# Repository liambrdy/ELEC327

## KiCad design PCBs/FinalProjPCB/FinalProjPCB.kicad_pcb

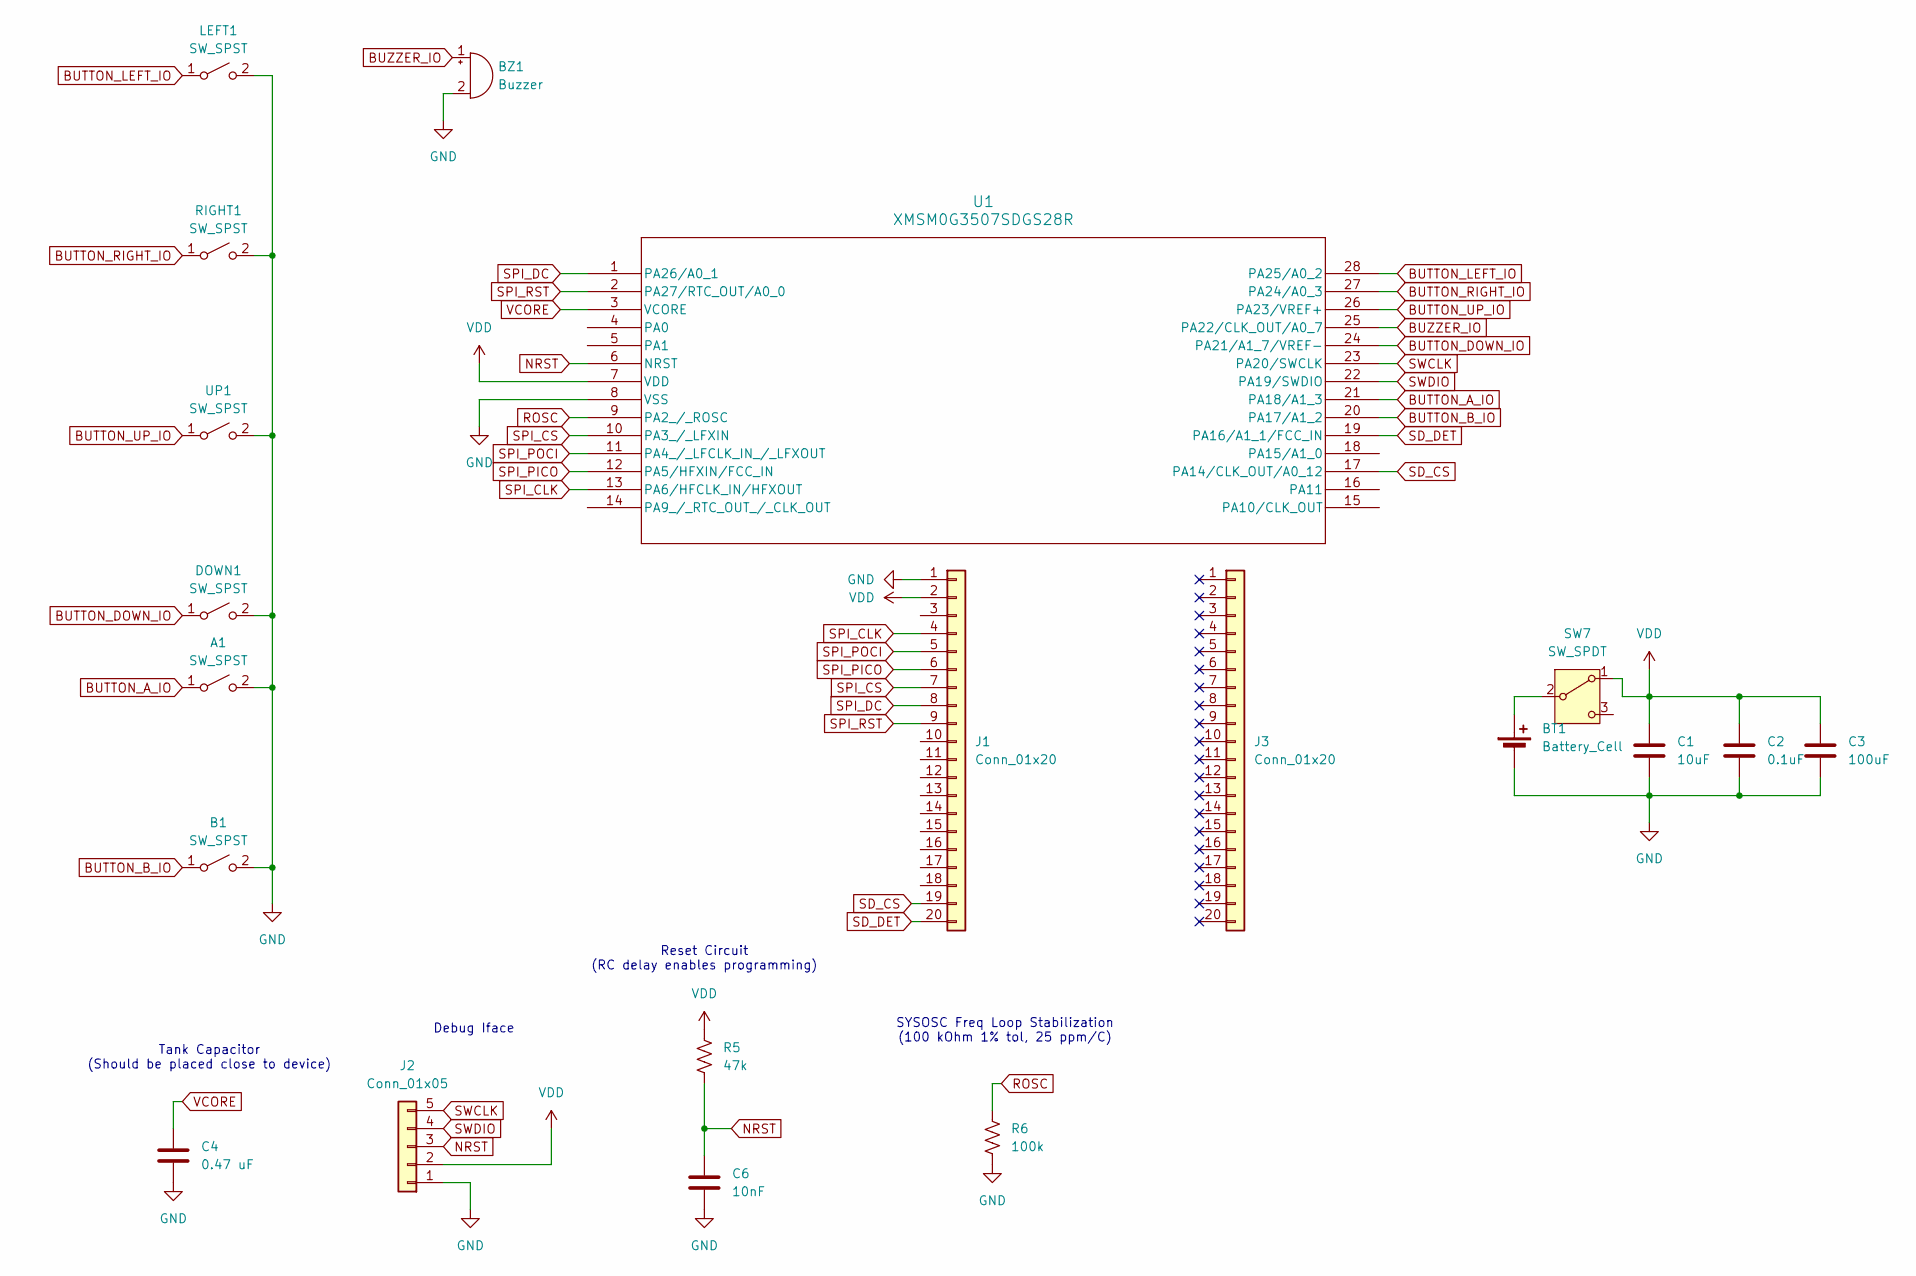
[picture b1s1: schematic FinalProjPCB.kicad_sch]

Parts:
A1: SW_SPST; SW_SPST_PTS647_Sx38; MPN C2799279; LCSC Part # C2799279
B1: SW_SPST; SW_SPST_PTS647_Sx38; MPN C2799279; LCSC Part # C2799279
BT1: Battery_Cell; BatteryHolder_Keystone_1060_1x2032; MPN C7498148; LCSC Part # C7498148
BZ1: Buzzer; Buzzer_Murata_PKLCS1212E; LCSC Part # C113159
C1: 10uF; C_0603_1608Metric; LCSC Part # C19702
C2: 0.1uF; C_0603_1608Metric_Pad1.08x0.95mm_HandSolder; LCSC Part # C1591
C3: 100uF; C_1206_3216Metric; LCSC Part # C15008
C4: 0.47 uF; C_0805_2012Metric; LCSC Part # C13967
C6: 10nF; C_0402_1005Metric; LCSC Part # C15195
DOWN1: SW_SPST; SW_SPST_PTS647_Sx38; MPN C2799279; LCSC Part # C2799279
J1, J3: Conn_01x20; PinHeader_1x20_P2.54mm_Vertical
J2: Conn_01x05; PinHeader_1x05_P2.54mm_Horizontal; LCSC Part # C492413
LEFT1: SW_SPST; SW_SPST_PTS647_Sx38; MPN C2799279; LCSC Part # C2799279
R5: 47k; R_0603_1608Metric; LCSC Part # C105579
R6: 100k; R_0402_1005Metric; LCSC Part # C60491
RIGHT1: SW_SPST; SW_SPST_PTS647_Sx38; MPN C2799279; LCSC Part # C2799279
SW7: SW_SPDT; SW_EG1270; MPN C20611678; LCSC Part # C20611678
U1: XMSM0G3507SDGS28R; VSSOP28_DGS_TEX
UP1: SW_SPST; SW_SPST_PTS647_Sx38; MPN C2799279; LCSC Part # C2799279

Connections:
BUTTON_A_IO: A1.1 (A), U1.21 (PA18/A1_3)
BUTTON_B_IO: B1.1 (A), U1.20 (PA17/A1_2)
BUTTON_DOWN_IO: DOWN1.1 (A), U1.24 (PA21/A1_7/VREF-)
BUTTON_LEFT_IO: LEFT1.1 (A), U1.28 (PA25/A0_2)
BUTTON_RIGHT_IO: RIGHT1.1 (A), U1.27 (PA24/A0_3)
BUTTON_UP_IO: U1.26 (PA23/VREF+), UP1.1 (A)
BUZZER_IO: BZ1.1 (+), U1.25 (PA22/CLK_OUT/A0_7)
GND: A1.2 (B), B1.2 (B), BT1.2 (-), BZ1.2 (-), C1.2, C2.2, C3.2, C4.2, C6.2, DOWN1.2 (B), J1.1, J2.1, LEFT1.2 (B), R6.1, RIGHT1.2 (B), U1.8 (VSS), UP1.2 (B)
NRST: C6.1, J2.3, R5.1, U1.6 (NRST)
unnamed: BT1.1 (+), SW7.2 (B)
ROSC: R6.2, U1.9 (PA2_/_ROSC)
SD_CS: J1.19, U1.17 (PA14/CLK_OUT/A0_12)
SD_DET: J1.20, U1.19 (PA16/A1_1/FCC_IN)
SPI_CLK: J1.4, U1.13 (PA6/HFCLK_IN/HFXOUT)
SPI_CS: J1.7, U1.10 (PA3_/_LFXIN)
SPI_DC: J1.8, U1.1 (PA26/A0_1)
SPI_PICO: J1.6, U1.12 (PA5/HFXIN/FCC_IN)
SPI_POCI: J1.5, U1.11 (PA4_/_LFCLK_IN_/_LFXOUT)
SPI_RST: J1.9, U1.2 (PA27/RTC_OUT/A0_0)
SWCLK: J2.5, U1.23 (PA20/SWCLK)
SWDIO: J2.4, U1.22 (PA19/SWDIO)
VCORE: C4.1, U1.3 (VCORE)
VDD: C1.1, C2.1, C3.1, J1.2, J2.2, R5.2, SW7.1 (A), U1.7 (VDD)

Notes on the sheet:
SYSOSC Freq Loop Stabilization (100 kOhm 1% tol, 25 ppm/C)
Reset Circuit (RC delay enables programming)
Debug Iface
Tank Capacitor (Should be placed close to device)

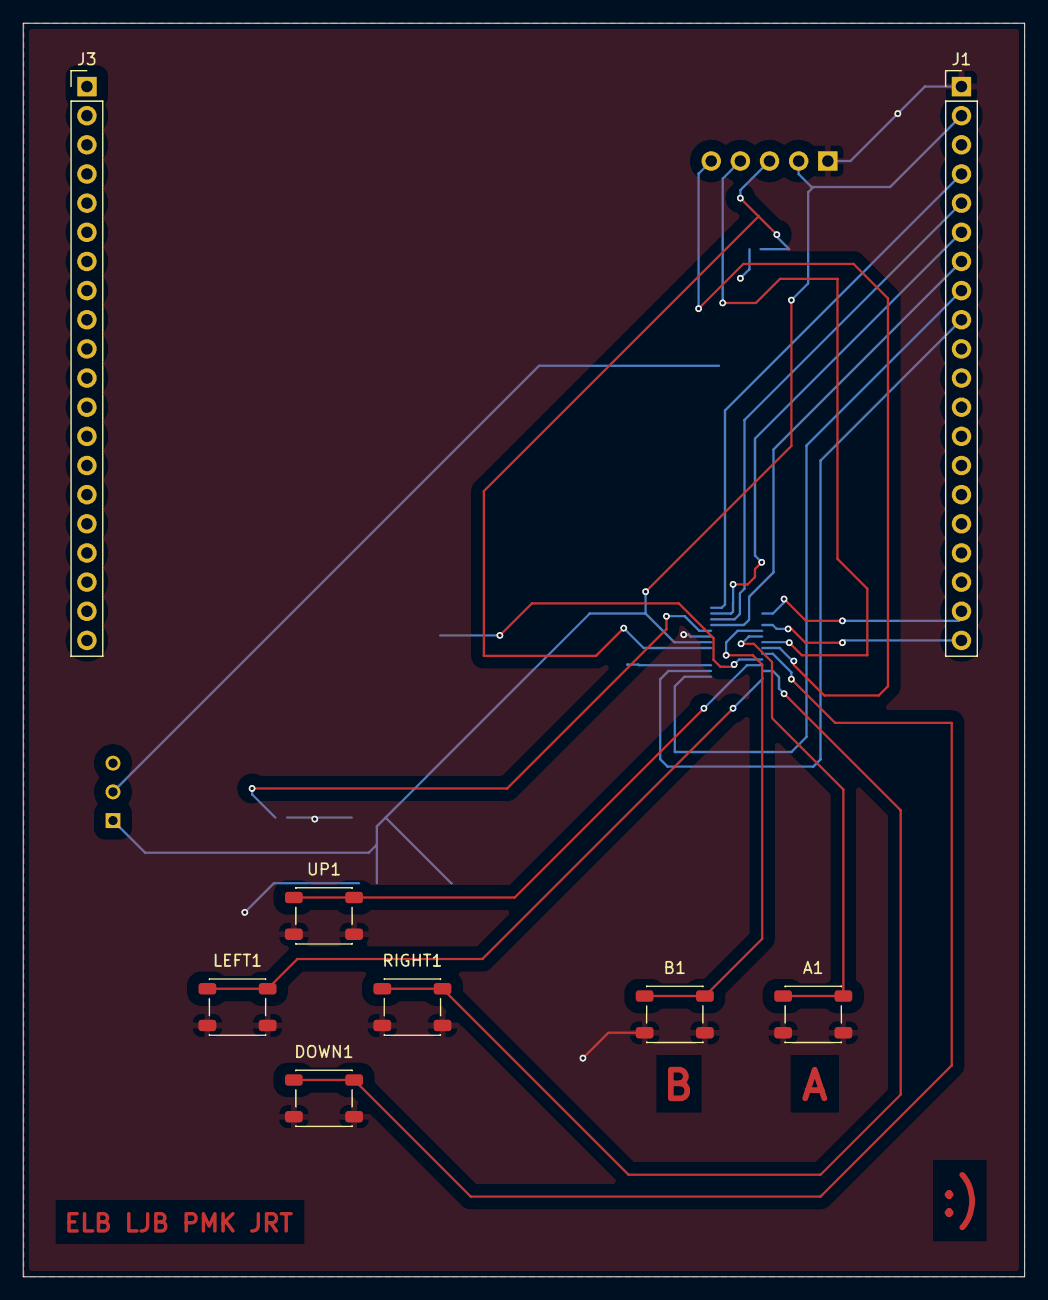
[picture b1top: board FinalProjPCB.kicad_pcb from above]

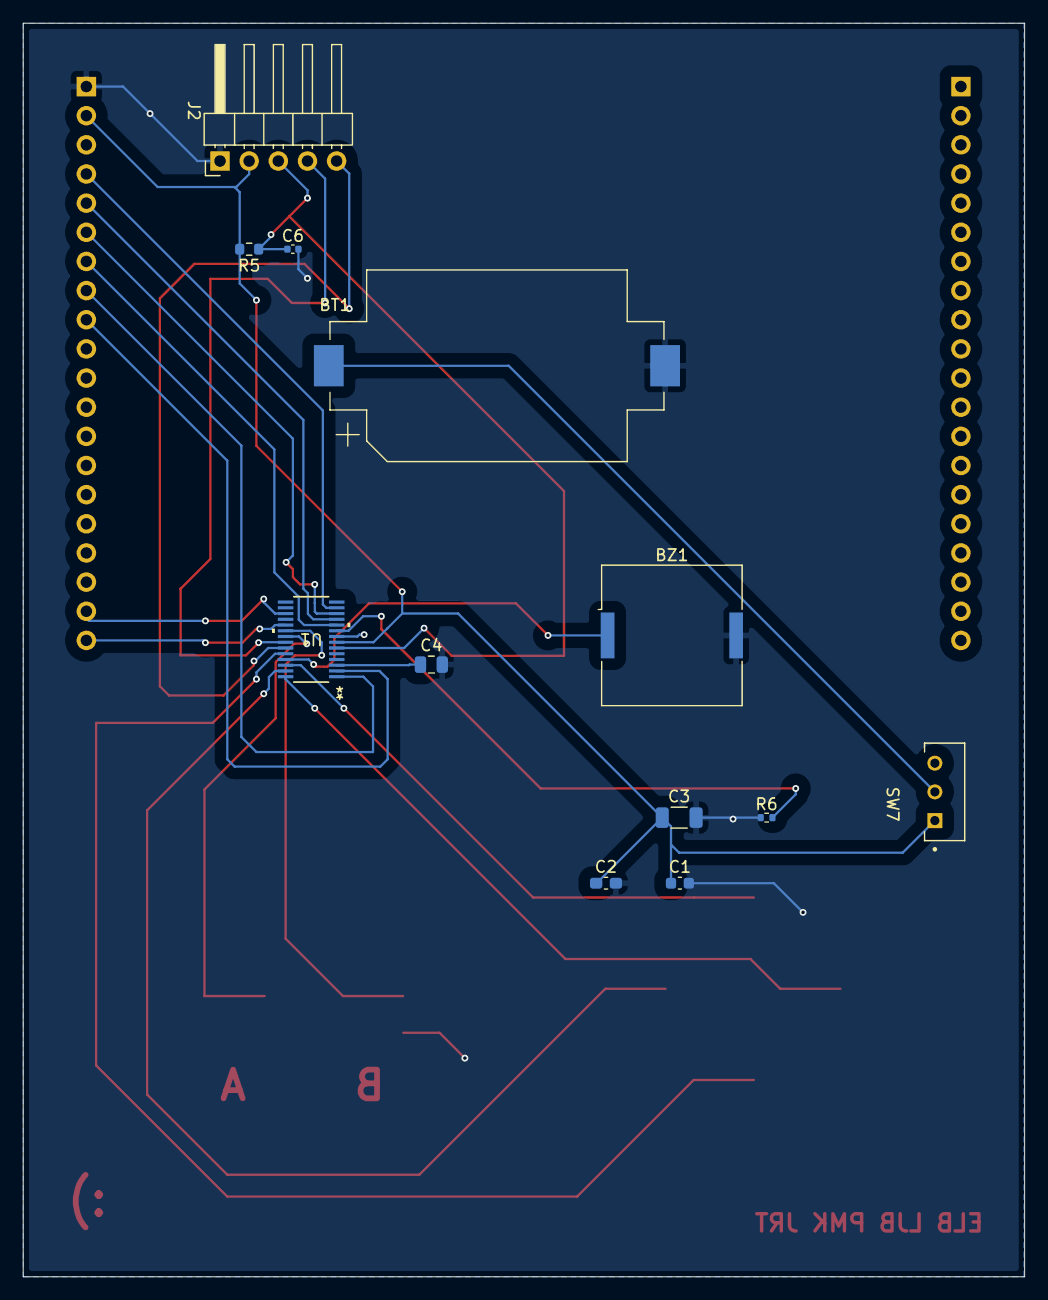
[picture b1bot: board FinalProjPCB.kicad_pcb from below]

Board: 2 copper layers, 87.2 x 109.2 mm, 20 parts (12 on the bottom side), 23 nets.

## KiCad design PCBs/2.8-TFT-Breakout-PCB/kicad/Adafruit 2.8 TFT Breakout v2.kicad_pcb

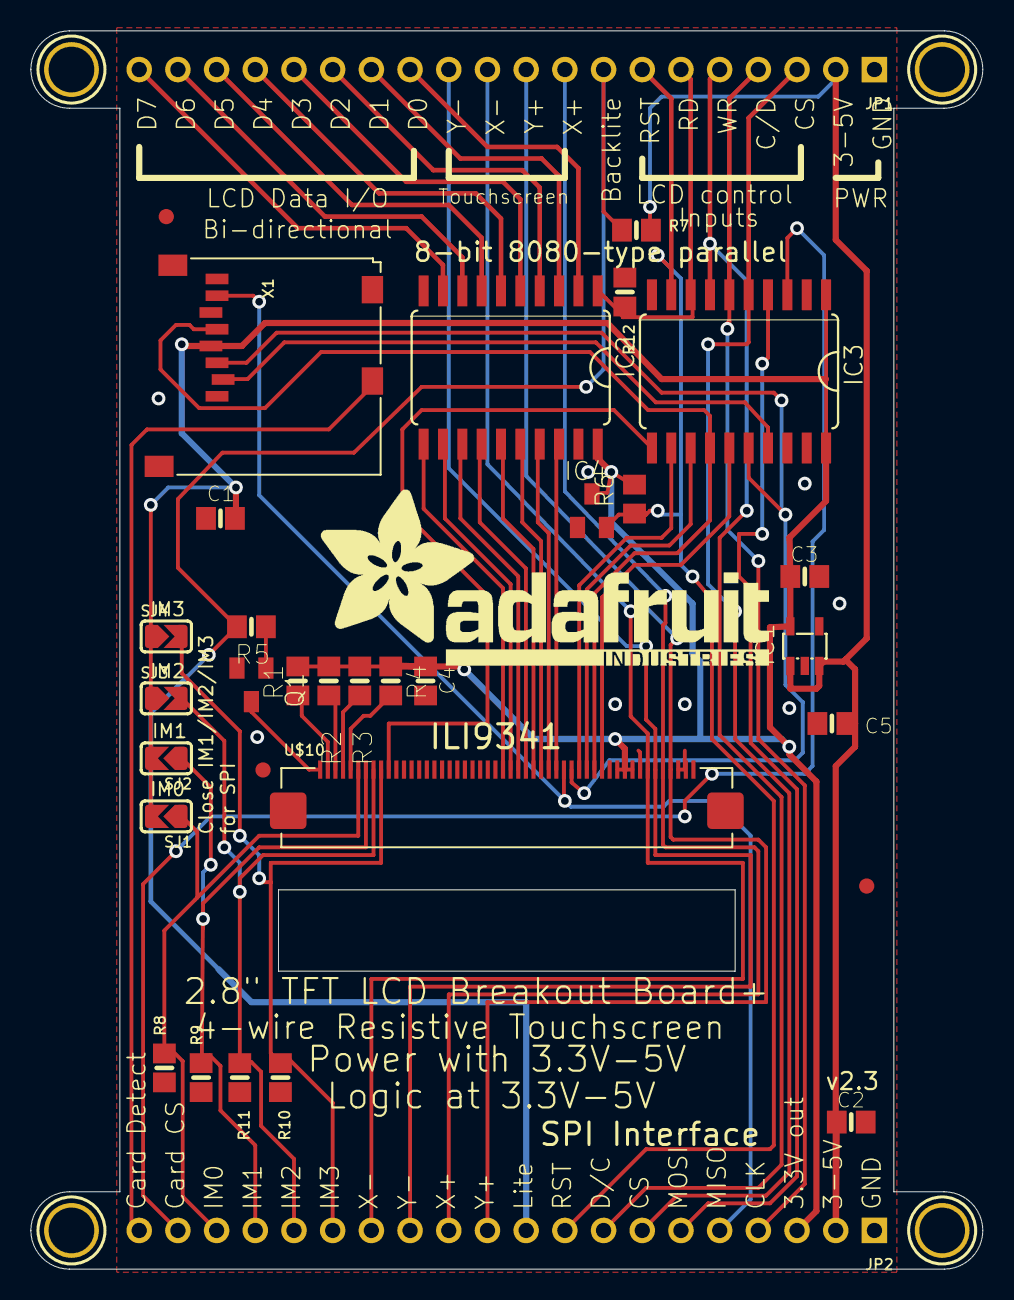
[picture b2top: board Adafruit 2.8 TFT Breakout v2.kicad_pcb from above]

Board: 16 copper layers, 62.5 x 81.3 mm, 38 parts (1 on the bottom side), 50 nets.

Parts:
C1, C4: 0.1uF; 0805-NO
C2, C3, C5: 10uF; 0805-NO
IC1: MIC5225-3.3; SOT23-5L
IC2, IC3: 74LVC245; SO20W
IC4: APX803-SAG; SOT23
JP1, JP2: 1X20_ROUND
Q1: MMBT2222; SOT23-BEC
R1, R2, R3, R4: 10; 0805-NO
R5, R7: 1K; 0805-NO
R6: 10K; R0805
R8, R9, R10, R11, R12: 10K; 0805-NO
SJ1, SJ2, SJ3, SJ4: SOLDERJUMPER_ARROW_NOPASTE
U$7, U$15, U$16, U$17: MOUNTINGHOLE3.0THIN; MOUNTINGHOLE_3.0_PLATEDTHIN
U$9, U$11, U$23: FIDUCIAL; FIDUCIAL_1MM
U$10: DISP_LCD_1.28IN_240X320_50PIN; TFT_2.83IN_240X320_50PIN
U$19: ADAFRUIT_TEXT_30MM
X1: MICROSD

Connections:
+5V: C2.1, C5.1, IC1.1, IC1.3, JP1.2, JP2.2, R7.2
CARDDET: JP2.20, X1.CD2
GND: C1.2, C2.2, C3.2, C4.2, C5.2, IC1.2, IC2.10, IC2.19, IC3.10, IC3.19, IC4.1, JP1.1, JP2.1, Q1.E, R8.1, R9.1, R10.2, R11.2, R12.1, U$10.43, U$10.48, U$10.49, U$10.50, X1.6, X1.MT1, X1.MT2
IM0: JP2.18, R8.2, SJ1.1, U$10.6
IM1: JP2.17, R9.2, SJ2.1, U$10.7
IM2: JP2.16, R11.1, SJ3.2, U$10.8
IM3: JP2.15, R10.1, SJ4.2, U$10.9
LCD_CS: IC3.15, U$10.38
LCD_CS_5V: IC3.5, JP1.3, JP2.7
LCD_DATA0: IC2.18, U$10.32
LCD_DATA0_5V: IC2.2, JP1.13
LCD_DATA1: IC2.17, U$10.31
LCD_DATA1_5V: IC2.3, JP1.14
LCD_DATA2: IC2.16, U$10.30
LCD_DATA2_5V: IC2.4, JP1.15
LCD_DATA3: IC2.15, U$10.29
LCD_DATA3_5V: IC2.5, JP1.16
LCD_DATA4: IC2.14, U$10.28
LCD_DATA4_5V: IC2.6, JP1.17
LCD_DATA5: IC2.13, U$10.27
LCD_DATA5_5V: IC2.7, JP1.18
LCD_DATA6: IC2.12, U$10.26
LCD_DATA6_5V: IC2.8, JP1.19
LCD_DATA7: IC2.11, U$10.25
LCD_DATA7_5V: IC2.9, JP1.20
LCD_LITE: JP1.8, JP2.10, R5.1, R7.1
LCD_RD: IC3.12, U$10.35
LCD_RD_5V: IC2.1, IC3.8, JP1.6, R12.2
LCD_RS: IC3.14, U$10.37, X1.5
LCD_RST: IC3.11, U$10.10
LCD_RST_5V: IC3.9, IC4.2, JP1.7, JP2.9, R6.1
LCD_RS_5V: IC3.6, JP1.4, JP2.4
LCD_WR: IC3.13, U$10.36
LCD_WR_5V: IC3.7, JP1.5, JP2.8
LCD_X+: JP1.9, JP2.12, U$10.46
LCD_X-: JP1.11, JP2.14, U$10.44
LCD_Y+: JP1.10, JP2.11, U$10.47
LCD_Y-: JP1.12, JP2.13, U$10.45
unnamed: R4.2, U$10.5
unnamed: R1.2, U$10.2
unnamed: R2.2, U$10.3
unnamed: R3.2, U$10.4
unnamed: Q1.C, U$10.1
unnamed: Q1.B, R5.2
SDI_3V: IC3.16, U$10.34, X1.3
SDI_5V: IC3.4, JP2.6
SDO: JP2.5, U$10.33, X1.7
SD_CS_3V: IC3.17, X1.2
SD_CS_5V: IC3.3, JP2.19
VCC: C1.1, C3.1, C4.1, IC1.5, IC2.20, IC3.1, IC3.20, IC4.3, JP2.3, R1.1, R2.1, R3.1, R4.1, R6.2, SJ1.2, SJ2.2, SJ3.1, SJ4.1, U$10.40, U$10.41, U$10.42, X1.4

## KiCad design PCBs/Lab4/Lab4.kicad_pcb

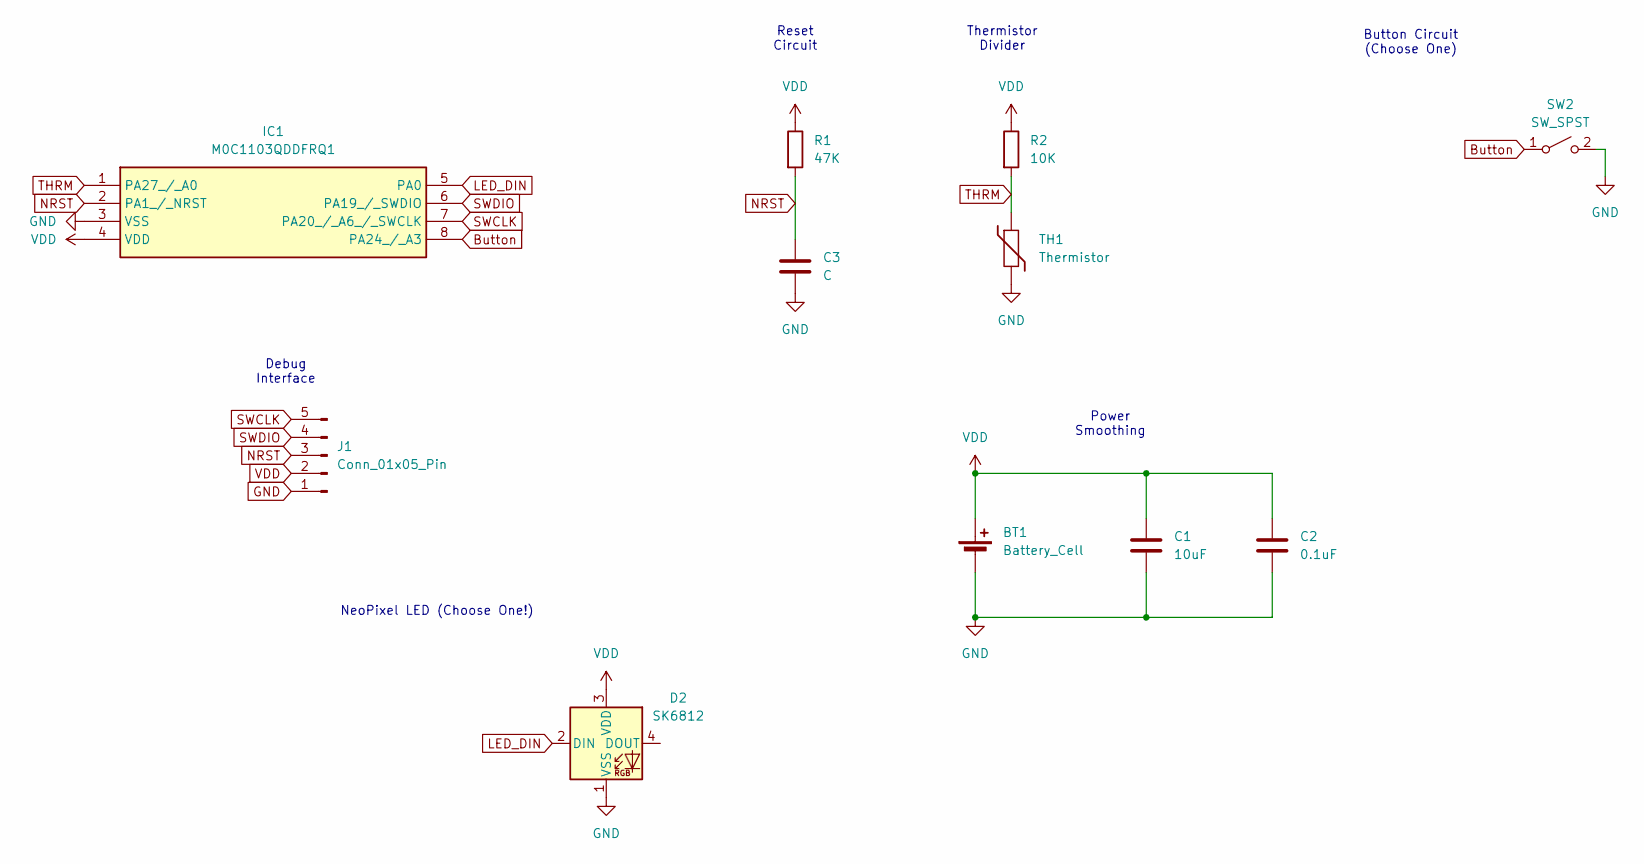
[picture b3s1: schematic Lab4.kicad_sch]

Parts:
BT1: Battery_Cell; BatteryHolder_Keystone_3001_1x12mm
C1: 10uF; C_1206_3216Metric_Pad1.33x1.80mm_HandSolder
C2: 0.1uF; C_1206_3216Metric_Pad1.33x1.80mm_HandSolder
C3: C; C_1206_3216Metric_Pad1.33x1.80mm_HandSolder
D2: SK6812; LED_SK6812_PLCC4_5.0x5.0mm_P3.2mm
IC1: M0C1103QDDFRQ1; SOT-23-8; Mouser Part Number 595-M0C1103QDDFRQ1
J1: Conn_01x05_Pin; PinHeader_1x05_P2.54mm_Vertical
R1: 47K; R_1206_3216Metric_Pad1.30x1.75mm_HandSolder
R2: 10K; R_1206_3216Metric_Pad1.30x1.75mm_HandSolder
SW2: SW_SPST; SW_SPST_PTS647_Sx50
TH1: Thermistor; R_1206_3216Metric_Pad1.30x1.75mm_HandSolder

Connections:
Button: IC1.8 (PA24_/_A3), SW2.1 (A)
GND: BT1.2 (-), C1.2, C2.2, C3.2, D2.1 (VSS), IC1.3 (VSS), J1.1, SW2.2 (B), TH1.2
LED_DIN: D2.2 (DIN), IC1.5 (PA0)
NRST: C3.1, IC1.2 (PA1_/_NRST), J1.3, R1.2
SWCLK: IC1.7 (PA20_/_A6_/_SWCLK), J1.5
SWDIO: IC1.6 (PA19_/_SWDIO), J1.4
THRM: IC1.1 (PA27_/_A0), R2.2, TH1.1
VDD: BT1.1 (+), C1.1, C2.1, D2.3 (VDD), IC1.4 (VDD), J1.2, R1.1, R2.1

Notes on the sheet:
Reset Circuit
NeoPixel LED (Choose One!)
Power Smoothing
Debug Interface
Thermistor Divider
Button Circuit (Choose One)

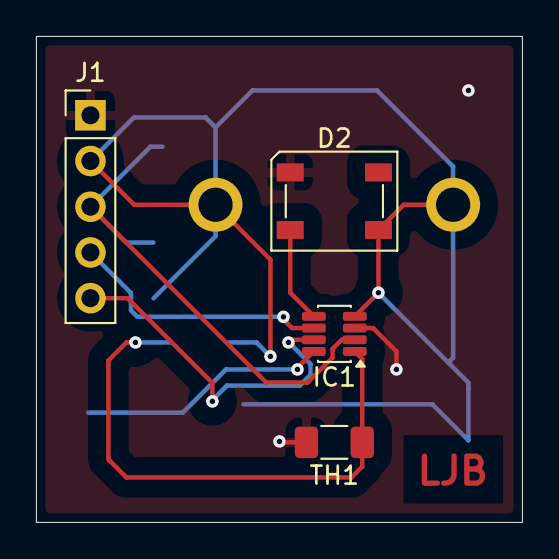
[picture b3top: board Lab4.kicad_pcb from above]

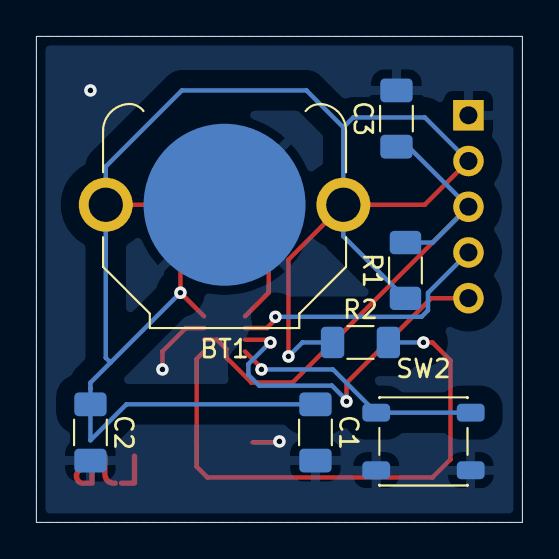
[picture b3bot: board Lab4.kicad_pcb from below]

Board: 2 copper layers, 27.0 x 27.0 mm, 11 parts (7 on the bottom side), 8 nets.

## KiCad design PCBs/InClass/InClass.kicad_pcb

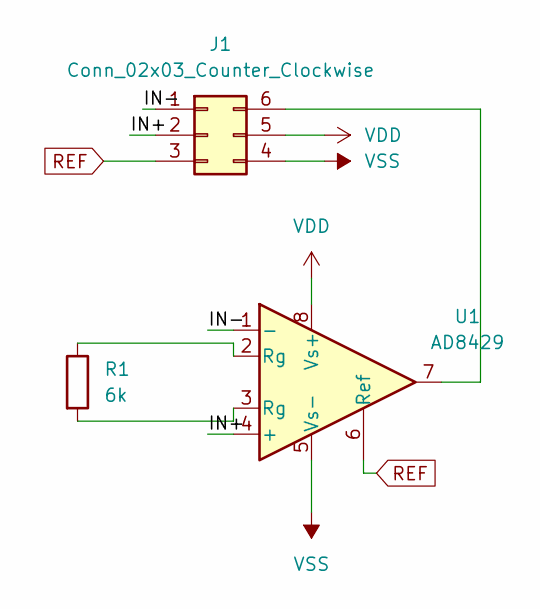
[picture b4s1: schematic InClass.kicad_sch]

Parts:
J1: Conn_02x03_Counter_Clockwise; PinHeader_2x03_P2.54mm_Vertical
R1: 6k; R_1206_3216Metric
U1: AD8429; SOIC-8-1EP_3.9x4.9mm_P1.27mm_EP2.29x3mm

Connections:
/IN+: J1.2, U1.4 (+)
/IN-: J1.1, U1.1 (-)
unnamed: J1.6, U1.7
unnamed: R1.1, U1.2 (Rg)
unnamed: R1.2, U1.3 (Rg)
REF: J1.3, U1.6 (Ref)
VDD: J1.5, U1.8 (Vs+)
VSS: J1.4, U1.5 (Vs-)

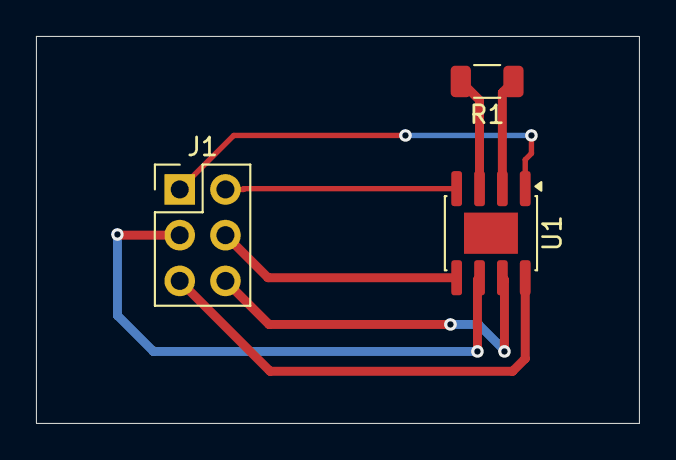
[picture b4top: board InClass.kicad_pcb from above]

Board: 2 copper layers, 33.5 x 21.5 mm, 3 parts (0 on the bottom side), 8 nets.

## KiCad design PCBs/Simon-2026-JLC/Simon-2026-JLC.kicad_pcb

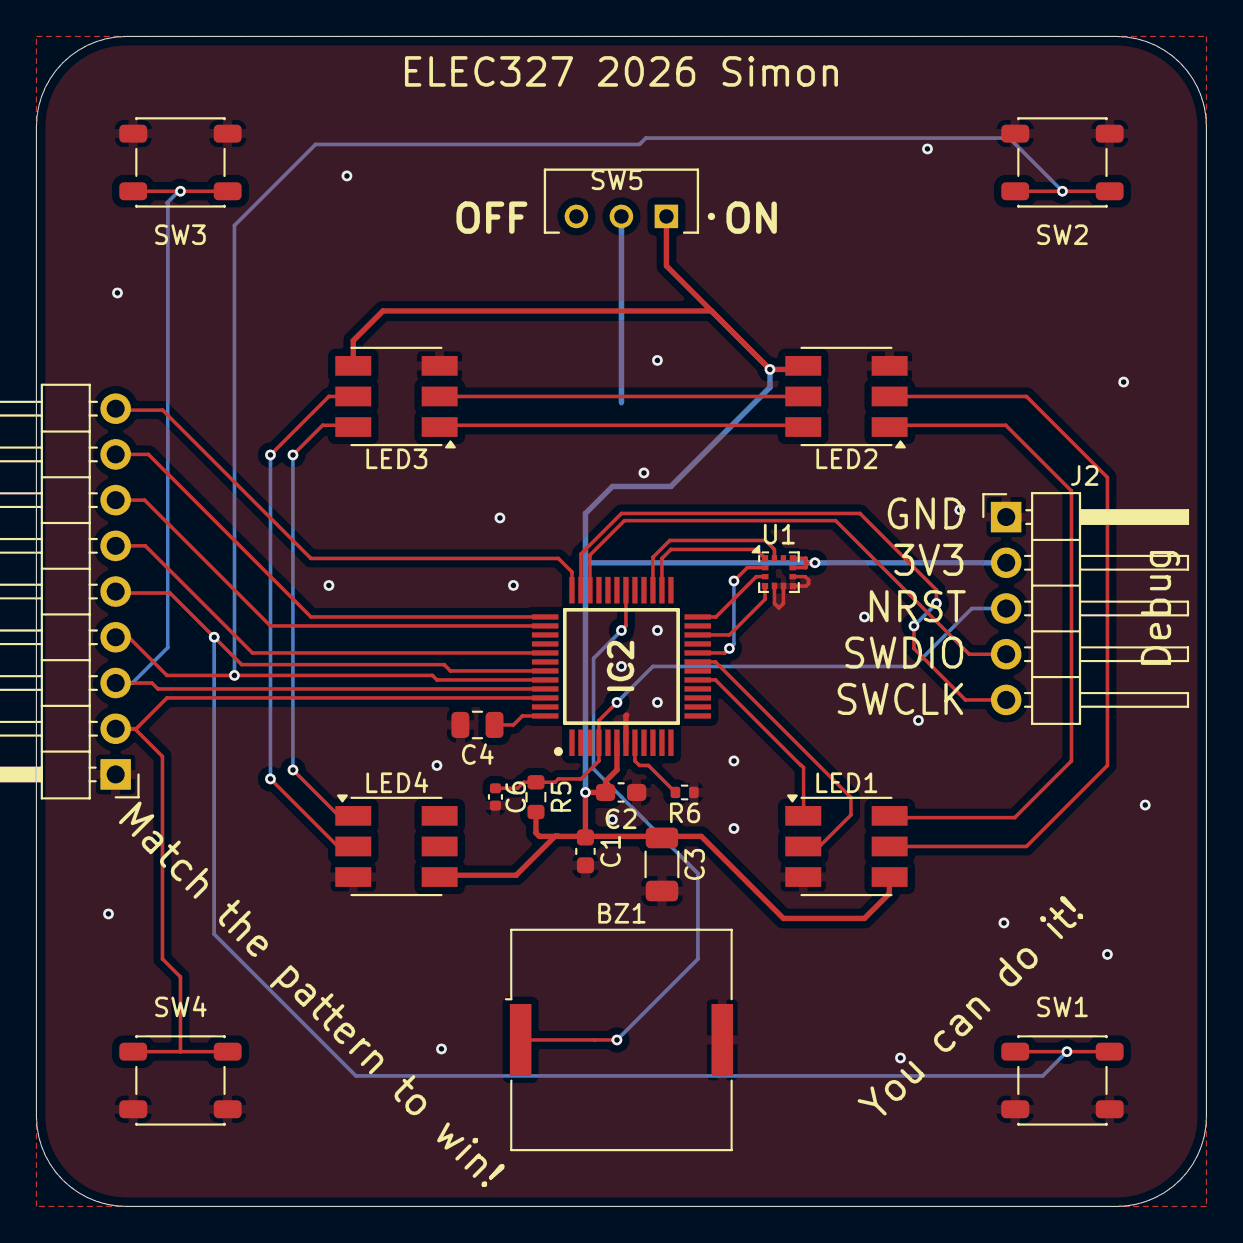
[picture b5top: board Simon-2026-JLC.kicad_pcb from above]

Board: 2 copper layers, 65.0 x 65.0 mm, 22 parts (1 on the bottom side), 30 nets.

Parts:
BT1: Battery_Cell; BatteryHolder_Keystone_1060_1x2032
BZ1: Buzzer; Buzzer_Murata_PKLCS1212E
C1: 10uF; C_0603_1608Metric
C2: 0.1uF; C_0603_1608Metric_Pad1.08x0.95mm_HandSolder
C3: 100uF; C_1206_3216Metric
C4: 0.47 uF; C_0805_2012Metric
C6: 10nF; C_0402_1005Metric
IC2: MSPM0G3507SPTR; QFP50P900X900X160-48N
J1: Conn_01x09; PinHeader_1x09_P2.54mm_Horizontal
J2: Conn_01x05; PinHeader_1x05_P2.54mm_Horizontal
LED1, LED2, LED3, LED4: SK9822; LED_RGB_5050-6
R5: 47k; R_0603_1608Metric
R6: 100k; R_0402_1005Metric
SW1, SW2, SW3, SW4: SW_SPST; SW_SPST_PTS647_Sx38
SW5: SW_SPDT; SW_EG1270
U1: LIS2HH12; LGA-12_2x2mm_P0.5mm

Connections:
ACC_INT: IC2.27 (PA12_/_FCC_IN), U1.12 (INT1)
BUTTON1_IO: IC2.43 (PA23_/_VREF+), J1.5, SW1.1 (A)
BUTTON2_IO: IC2.44 (PA24_/_A0_3), J1.4, SW2.1 (A)
BUTTON3_IO: IC2.45 (PA25_/_A0_2_/_OPA0_IN1+), J1.3, SW3.1 (A)
BUTTON4_IO: IC2.46 (PA26_/_A0_1), J1.2, SW4.1 (A)
BUZZER_IO: BZ1.1 (+), IC2.30 (PA15_/_A1_0/DAC_OUT)
GND: BT1.2 (-), BZ1.2 (-), C1.2, C2.2, C3.2, C4.2, C6.2, IC2.7 (VSS), J1.1, J2.1, LED1.3 (GND), LED2.3 (GND), LED3.3 (GND), LED4.3 (GND), R6.1, SW1.2 (B), SW2.2 (B), SW3.2 (B), SW4.2 (B), U1.5 (RES), U1.6 (GND), U1.7 (GND), U1.8 (GND)
LED1_IO: IC2.36 (PB17_/_A1_4), J1.9
LED2_IO: IC2.37 (PB18_/_A1_5), J1.8
LED3_IO: IC2.38 (PB19_/_A1_6), J1.7
LED4_IO: IC2.41 (PB20_/_A0_6), J1.6
NRST: C6.1, IC2.4 (NRST), J2.3, R5.1
unnamed: BT1.1 (+), SW5.2 (B)
unnamed: LED1.5 (COUT), LED2.2 (CIN)
unnamed: LED1.6 (DOUT), LED2.1 (DIN)
unnamed: LED2.5 (COUT), LED3.2 (CIN)
unnamed: LED2.6 (DOUT), LED3.1 (DIN)
unnamed: LED3.5 (COUT), LED4.2 (CIN)
unnamed: LED3.6 (DOUT), LED4.1 (DIN)
ROSC: IC2.8 (PA2_/_ROSC), R6.2
SPI0_LED_PICO: IC2.17 (PA9_/_RTC_OUT_/_CLK_OUT), LED1.1 (DIN)
SPI0_LED_SCK: IC2.19 (PA11), LED1.2 (CIN)
SPI1_CS0: IC2.20 (PB6), U1.2 (~CS)
SPI1_PICO: IC2.22 (PB8), U1.4 (SDA/SDI)
SPI1_POCI: IC2.24 (PB14), U1.3 (SA0/SDO)
SPI1_SCK: IC2.26 (PB16), U1.1 (SCL/SPC)
SWCLK: IC2.35 (PA20_/_SWCLK), J2.5
SWDIO: IC2.34 (PA19_/_SWDIO), J2.4
VCORE: C4.1, IC2.48 (VCORE)
VDD: C1.1, C2.1, C3.1, IC2.6 (VDD), J2.2, LED1.4 (VCC), LED2.4 (VCC), LED3.4 (VCC), LED4.4 (VCC), R5.2, SW5.1 (A), U1.9 (Vdd), U1.10 (Vdd_IO)

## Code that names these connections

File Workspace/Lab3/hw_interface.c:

#include <ti/devices/msp/msp.h>
#include "hw_interface.h"

#define POWER_STARTUP_DELAY (32)

int led_mask; // Used to remember which pins are used for LEDs

pin_config_t hour_leds[12] = {
    { .pin_number = 0,  .iomux = 1  },  // PA0
    { .pin_number = 26, .iomux = 59 },  // PA26
    { .pin_number = 24, .iomux = 54 },  // PA24
    { .pin_number = 22, .iomux = 47 },  // PA22
    { .pin_number = 18, .iomux = 40 },  // PA18
    { .pin_number = 16, .iomux = 38 },  // PA16
    { .pin_number = 14, .iomux = 36 },  // PA14
    { .pin_number = 12, .iomux = 34 },  // PA12
    { .pin_number = 10, .iomux = 21 },  // PA10
    { .pin_number = 8,  .iomux = 19 },  // PA8
    { .pin_number = 6,  .iomux = 11 },  // PA6
    { .pin_number = 28, .iomux = 3  },  // PA28
};

pin_config_t minute_leds[12] = {
    { .pin_number = 27, .iomux = 60 },  // PA27
    { .pin_number = 25, .iomux = 55 },  // PA25
    { .pin_number = 23, .iomux = 53 },  // PA23
    { .pin_number = 21, .iomux = 46 },  // PA21
    { .pin_number = 17, .iomux = 39 },  // PA17
    { .pin_number = 15, .iomux = 37 },  // PA15
    { .pin_number = 13, .iomux = 35 },  // PA13
    { .pin_number = 11, .iomux = 22 },  // PA11
    { .pin_number = 9,  .iomux = 20 },  // PA9
    { .pin_number = 7,  .iomux = 14 },  // PA7
    { .pin_number = 5,  .iomux = 10 },  // PA5
    { .pin_number = 1,  .iomux = 2  },  // PA1
};

pin_config_t button = { .pin_number = 8, .iomux = 25 };

void delay_cycles(uint32_t cycles)
{
    /* this is a scratch register for the compiler to use */
    uint32_t scratch;

    /* There will be a 2 cycle delay here to fetch & decode instructions
     * if branch and linking to this function */

    /* Subtract 2 net cycles for constant offset: +2 cycles for entry jump,
     * +2 cycles for exit, -1 cycle for a shorter loop cycle on the last loop,
     * -1 for this instruction */

    __asm volatile(
#ifdef __GNUC__
        ".syntax unified\n\t"
#endif
        "SUBS %0, %[numCycles], #2; \n"
        "%=: \n\t"
        "SUBS %0, %0, #4; \n\t"
        "NOP; \n\t"
        "BHS  %=b;" /* branches back to the label defined above if number > 0 */
        /* Return: 2 cycles */
        : "=&r"(scratch)
        : [ numCycles ] "r"(cycles));
}


// TODO: Fill in the implementation here!
void InitializeButton() {
    GPIOB->GPRCM.RSTCTL = (GPIO_RSTCTL_KEY_UNLOCK_W | GPIO_RSTCTL_RESETSTKYCLR_CLR | GPIO_RSTCTL_RESETASSERT_ASSERT);
    GPIOB->GPRCM.PWREN = (GPIO_PWREN_KEY_UNLOCK_W | GPIO_PWREN_ENABLE_ENABLE);

    delay_cycles(POWER_STARTUP_DELAY);

    IOMUX->SECCFG.PINCM[button.iomux - 1] = (IOMUX_PINCM_PC_CONNECTED | IOMUX_PINCM_PIPU_ENABLE | IOMUX_PINCM_INENA_ENABLE | ((uint32_t) 0x00000001));
}

// TODO: Fill in the implementation here!
inline uint32_t GetButtonState() {
    return (GPIOB->DIN31_0 >> button.pin_number) & 0x1;
}

void InitializeLEDs() {
    // 1. Reset GPIO port (the one(s) for pins that you will use)
    GPIOA->GPRCM.RSTCTL = (GPIO_RSTCTL_KEY_UNLOCK_W | GPIO_RSTCTL_RESETSTKYCLR_CLR | GPIO_RSTCTL_RESETASSERT_ASSERT);

    // 2. Enable power on LED GPIO port
    GPIOA->GPRCM.PWREN = (GPIO_PWREN_KEY_UNLOCK_W | GPIO_PWREN_ENABLE_ENABLE);

    delay_cycles(POWER_STARTUP_DELAY); // delay to enable GPIO to turn on and reset

    // initialize pins for hours and minutes
    led_mask = 0;
    for (int i = 0; i < 12; i++) {
        // hours
        int iomux_entry = hour_leds[i].iomux - 1;
        IOMUX->SECCFG.PINCM[iomux_entry] = (IOMUX_PINCM_PC_CONNECTED | ((uint32_t) 0x00000001));
        GPIOA->DOUTSET31_0 = (0x1 << hour_leds[i].pin_number);
        GPIOA->DOESET31_0 = (0x1 << hour_leds[i].pin_number);

        led_mask |= (0x1 << hour_leds[i].pin_number);
        // minutes
        iomux_entry = minute_leds[i].iomux - 1;
        IOMUX->SECCFG.PINCM[iomux_entry] = (IOMUX_PINCM_PC_CONNECTED | ((uint32_t) 0x00000001));
        GPIOA->DOUTSET31_0 = (0x1 << minute_leds[i].pin_number);
        GPIOA->DOESET31_0 = (0x1 << minute_leds[i].pin_number);

        led_mask |= (0x1 << minute_leds[i].pin_number);
    }
}


void InitializeTimerG0() {

    /* Timer module and Sleep Mode Initialization */
    // 1. Step 1 is always to reset and enable
    TIMG0->GPRCM.RSTCTL = (GPIO_RSTCTL_KEY_UNLOCK_W | GPIO_RSTCTL_RESETSTKYCLR_CLR | GPIO_RSTCTL_RESETASSERT_ASSERT);
    TIMG0->GPRCM.PWREN = (GPIO_PWREN_KEY_UNLOCK_W | GPIO_PWREN_ENABLE_ENABLE);
    delay_cycles(16); // delay to enable module to turn on and reset

    // 2. Step 2 is to choose the desired clock. We want UPCLK (LFCLK) so we can use a LPM
    // TIMG0->CLKSEL = GPTIMER_CLKSEL_BUSCLK_SEL_ENABLE;
    TIMG0->CLKSEL = GPTIMER_CLKSEL_LFCLK_SEL_ENABLE;

    // 3. By default, the timer counts down to zero and then stops. Configure it to repeat.
    TIMG0->COUNTERREGS.CTRCTL = GPTIMER_CTRCTL_REPEAT_REPEAT_1;

    // 4. Enable timer interrupt when we reach 0
    TIMG0->CPU_INT.IMASK |= GPTIMER_CPU_INT_IMASK_Z_SET;

    // 5. Enable the clock input to the timer. (The timer itself is still not enabled!)
    TIMG0->COMMONREGS.CCLKCTL = GPTIMER_CCLKCTL_CLKEN_ENABLED;
    // 6. Set sleep to be STANDBY (Rev 2025 TRM p. 227, also 2.4.2 Operating Mode Selection)
    SYSCTL->SOCLOCK.PMODECFG = SYSCTL_PMODECFG_DSLEEP_STANDBY;
    SCB->SCR |= SCB_SCR_SLEEPDEEP_Msk;
    // Set sleep to be STANDBY1 (Rev 2025 TRM Table 2-9. MSPM0Gxx ULPCLK by Operating Mode)
    SYSCTL->SOCLOCK.MCLKCFG |= SYSCTL_MCLKCFG_STOPCLKSTBY_ENABLE;

}

inline void SetTimerG0Delay(uint16_t delay) {
    TIMG0->COUNTERREGS.LOAD = delay; // This will load as soon as timer is enabled
}

inline void EnableTimerG0() {
    TIMG0->COUNTERREGS.CTRCTL |= (GPTIMER_CTRCTL_EN_ENABLED);
    NVIC_EnableIRQ(TIMG0_INT_IRQn); // Enable the timer interrupt
}


// The function needs to be put into the interrupt table!!!!
void TIMG0_IRQHandler(void)
{
    // This wakes up the processor!
    switch (TIMG0->CPU_INT.IIDX) {
        case GPTIMER_CPU_INT_IIDX_STAT_Z: // Counted down to zero event.
            // If we wanted to execute code in the ISR, it would go here.
            break;
        default:
            break;
    }
}

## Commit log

2026-01-16 implemented lab 1
2026-01-25 finished lab1
2026-02-07 lab 2 implemented
2026-02-08 implemented lab3
2026-02-09 random stuff
2026-02-11 added stuff
2026-02-11 started working on rom compiler
2026-02-11 stopped tracking bad stuff
2026-02-14 more compiler stuff
2026-02-15 lab4 completed
2026-02-16 more proj stuff
2026-02-22 updated compiler stuff
2026-02-22 added tft display files
2026-02-22 platform stuff and initial decl
2026-02-25 implemented declaration parsing
2026-02-25 fully finished declarations
2026-02-25 implemented memory arena
2026-02-26 begin statement stuff
2026-02-27 PWM Lab5 implementation
2026-02-28 finished ast
2026-03-02 added preprocessors
2026-03-02 improvements
2026-03-03 rewrote lexer
2026-03-03 moved all strings to slices
2026-03-04 start semantic analysis
2026-03-04 worked on lab5
2026-03-05 lab6 + tft
2026-03-12 compiler stuff
2026-03-23 upload stuff
2026-03-24 added lab 6 stuff
2026-03-25 started on simon
2026-03-27 part of simon
2026-04-01 codegen
2026-04-06 stuff
2026-04-22 big proj updates
2026-04-22 more big stuff
2026-04-23 final proj crunch
2026-04-24 more stuff
2026-04-24 final proj pcb v1
2026-04-24 updated pcb
2026-04-27 getting closer
2026-05-05 new code
2026-05-05 final push
2026-05-05 buttons working

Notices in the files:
PCBs/Simon-2026-JLC/Simon-2026-JLC.kicad_pcb:
(c) 2026
